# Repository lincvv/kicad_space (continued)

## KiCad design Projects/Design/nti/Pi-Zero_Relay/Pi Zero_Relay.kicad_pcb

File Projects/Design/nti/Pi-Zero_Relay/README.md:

**Board with relay for Raspberry PI Zero. There is an installation place for the Arduino shield RS-485**

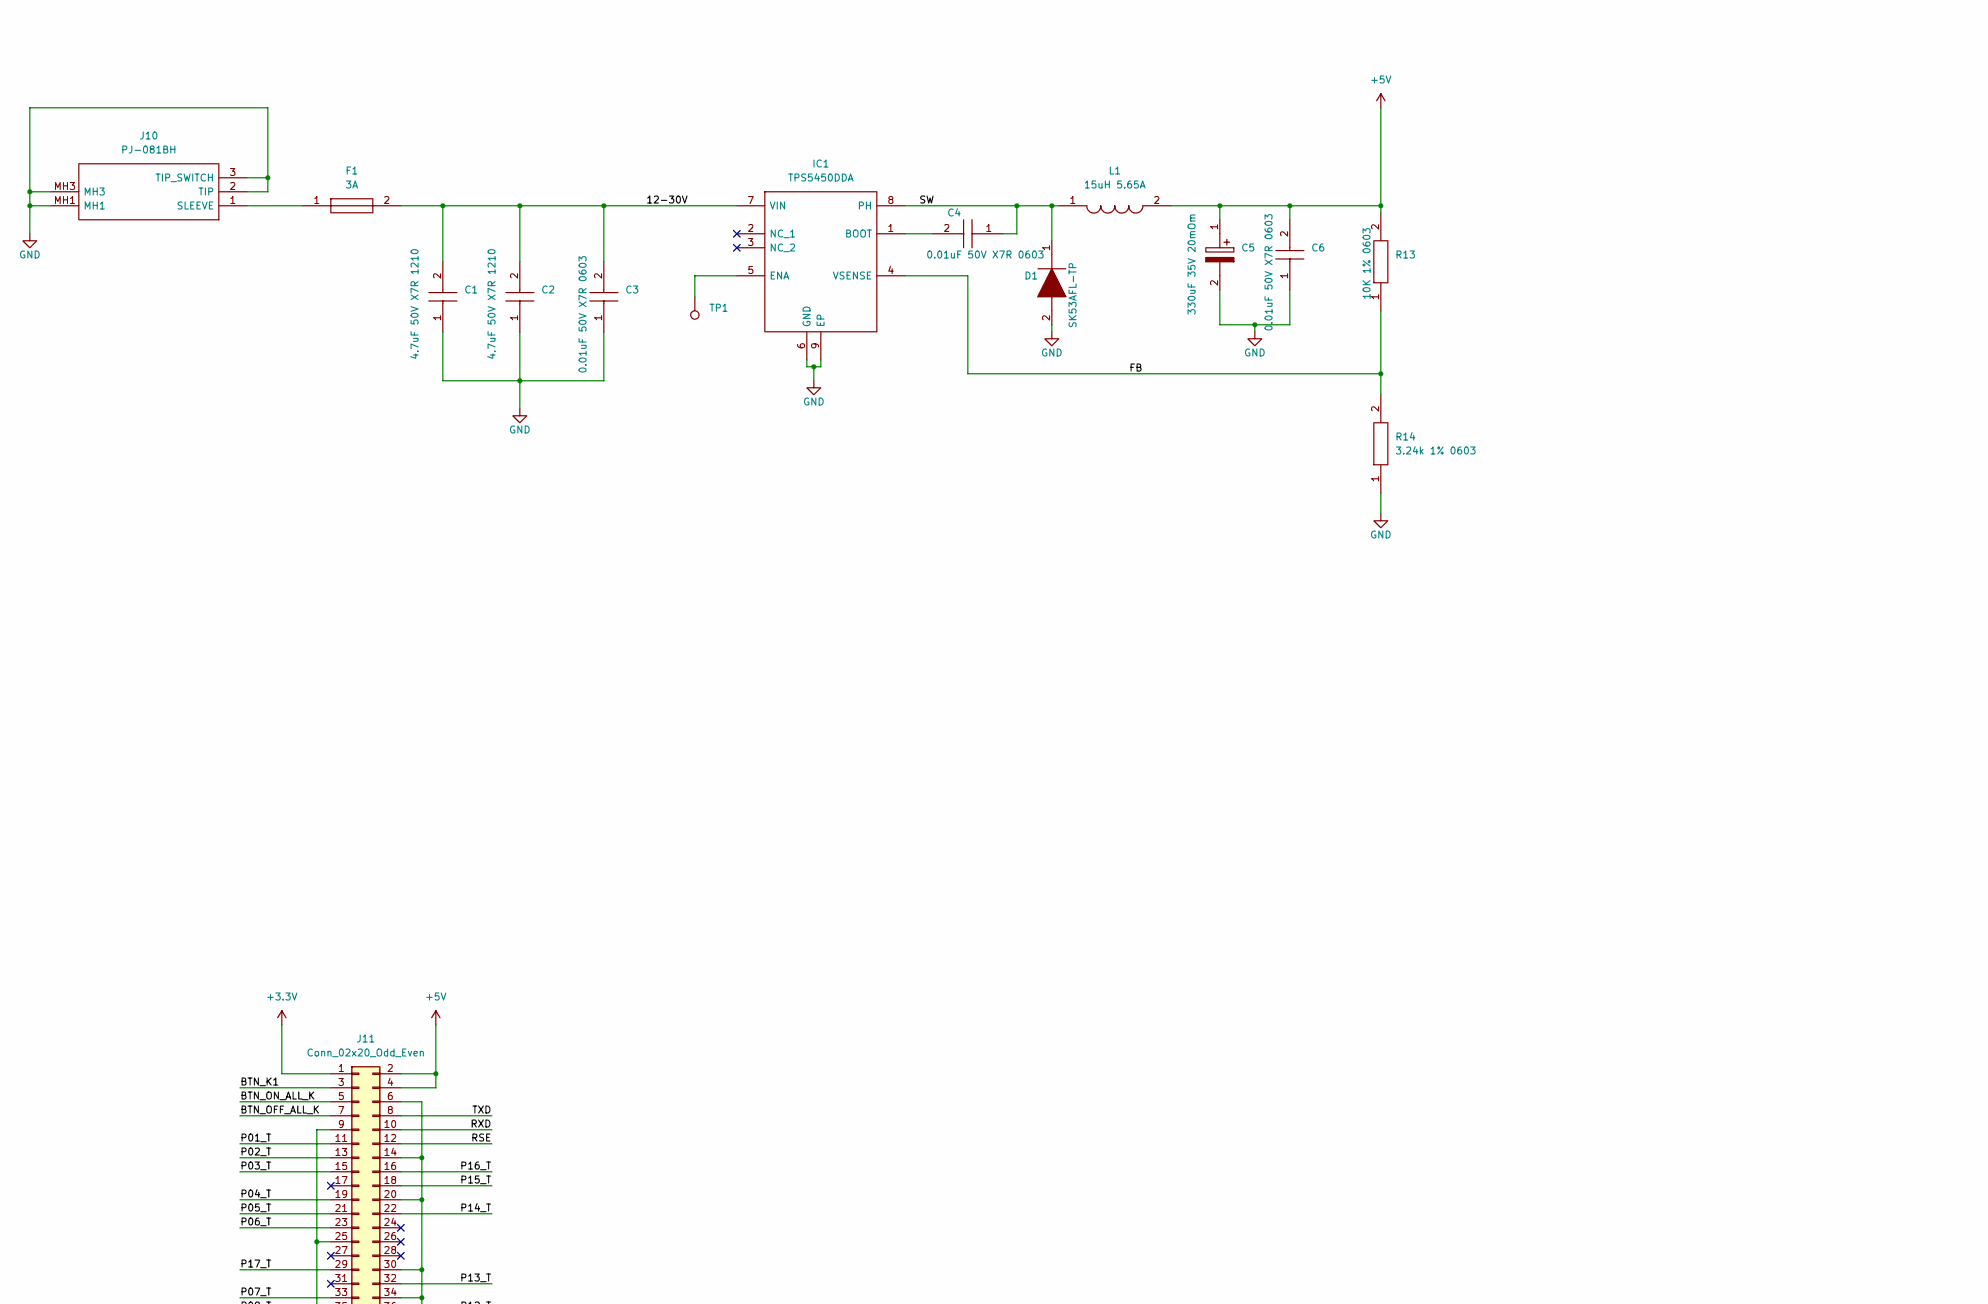
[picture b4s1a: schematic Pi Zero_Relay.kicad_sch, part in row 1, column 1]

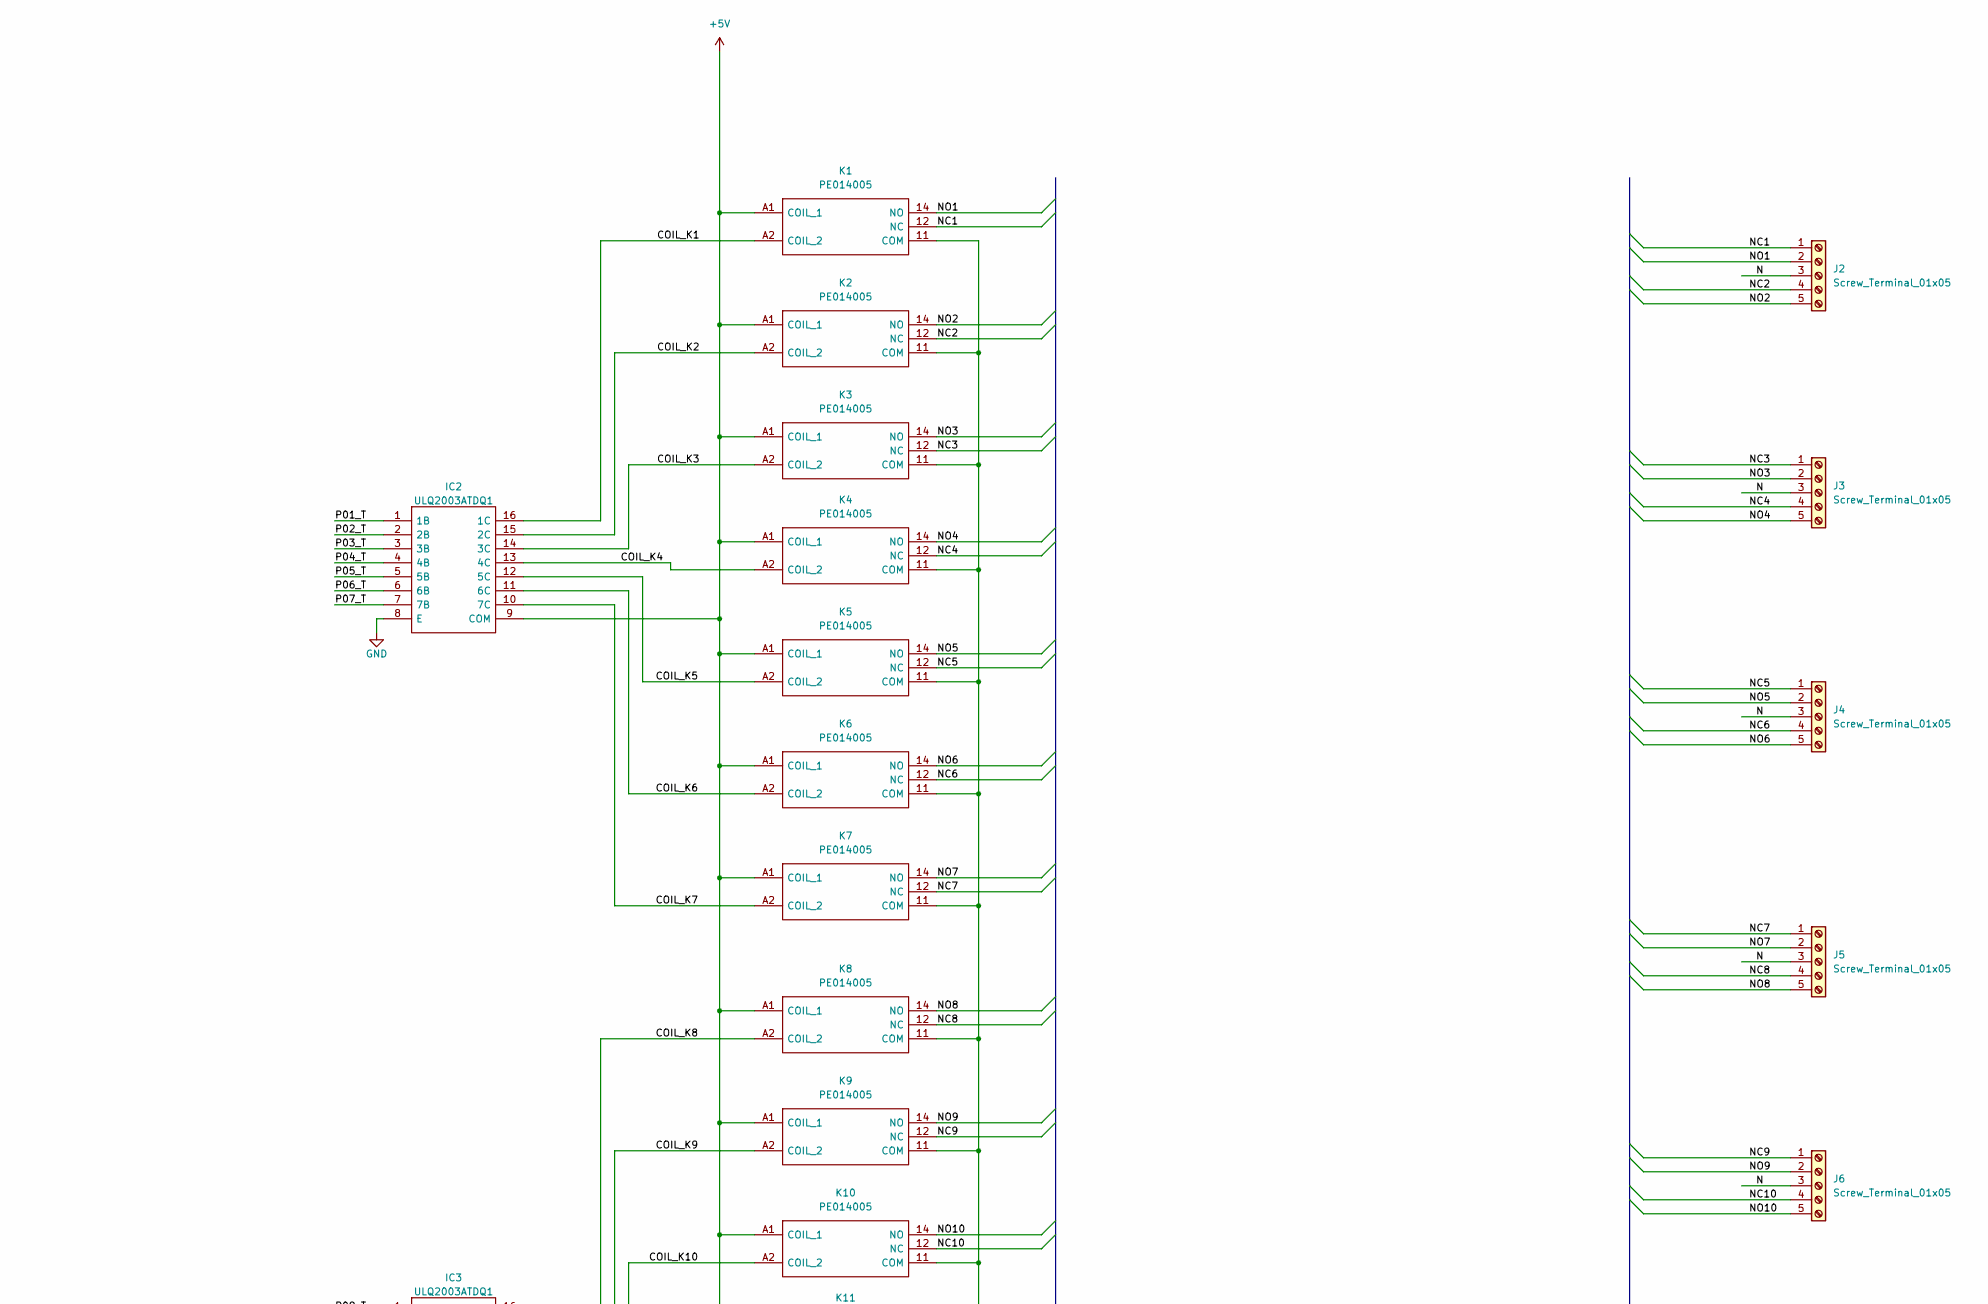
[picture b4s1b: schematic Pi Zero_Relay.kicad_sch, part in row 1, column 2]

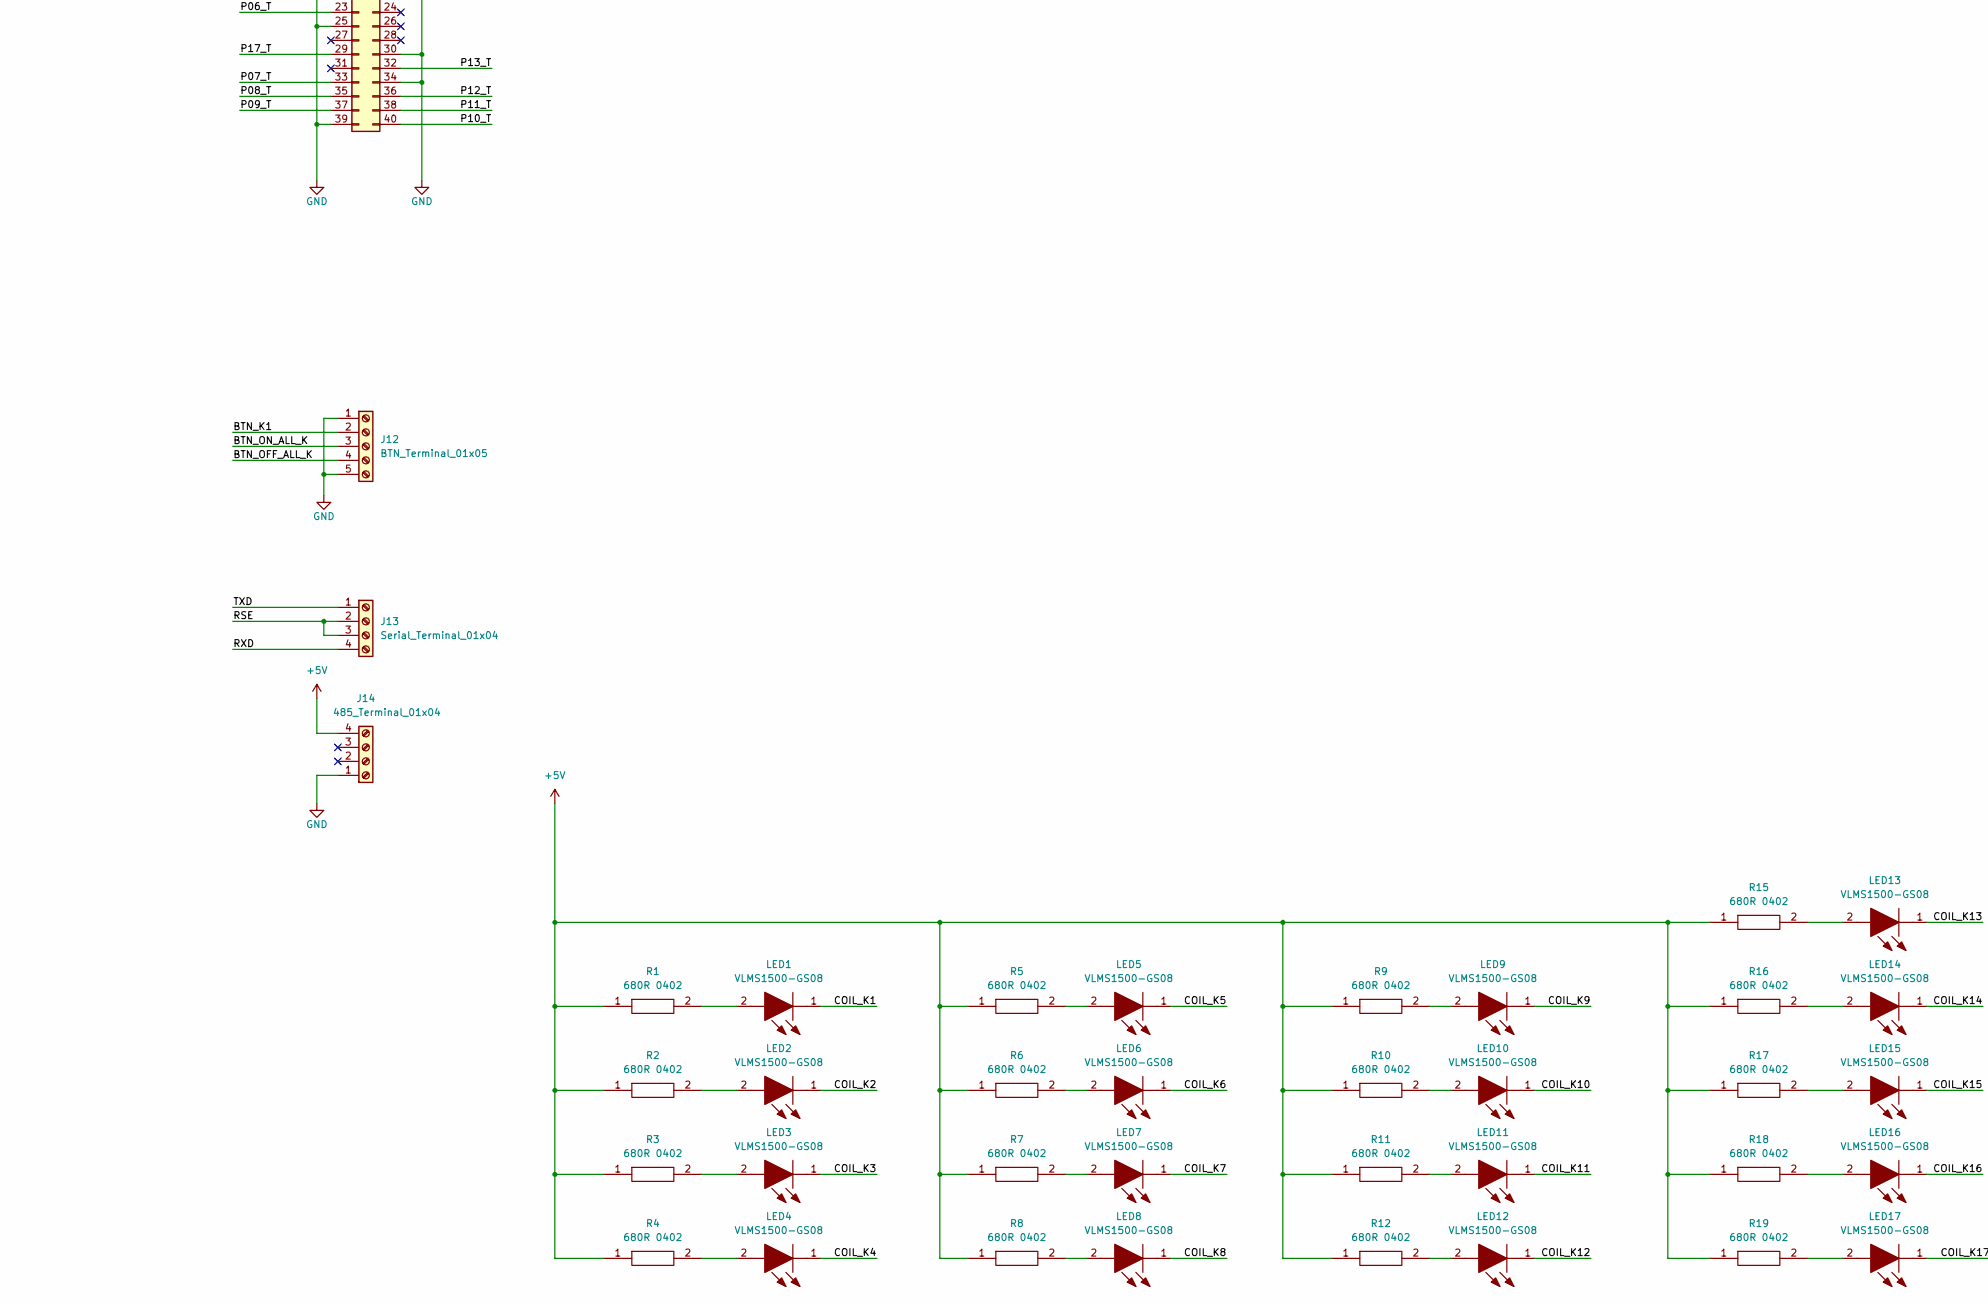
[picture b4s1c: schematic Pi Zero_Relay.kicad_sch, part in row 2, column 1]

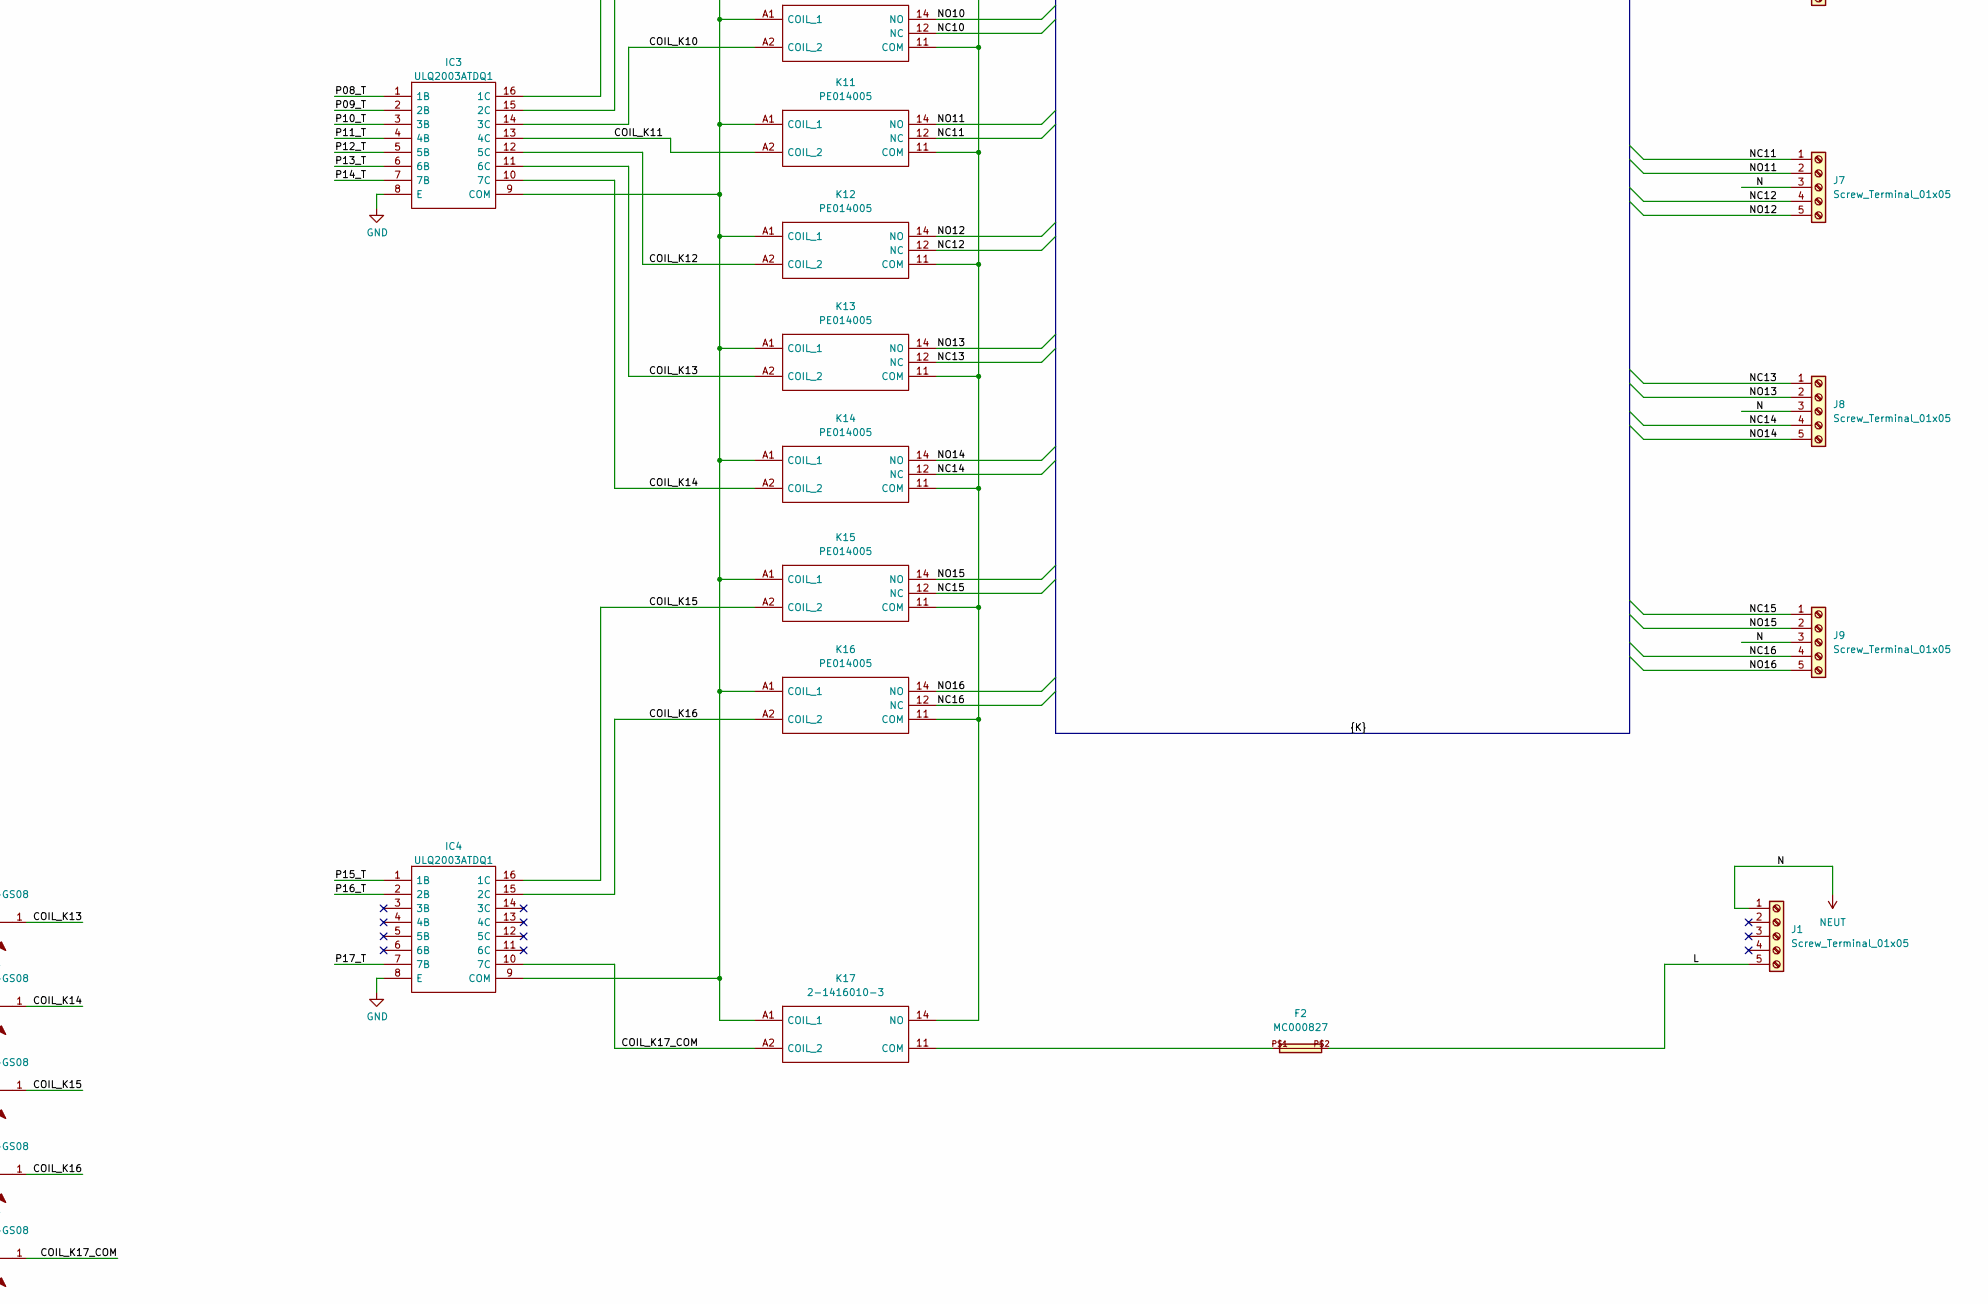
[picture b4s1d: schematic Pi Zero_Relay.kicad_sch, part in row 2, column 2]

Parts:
C1, C2: 4.7uF 50V X7R 1210; C_1210_3225Metric; Manufacturer_Part_Number CC1210KFX7R9BB475; Mouser Part Number 603-CC1210KFX7R9B475
C3, C4, C6: 0.01uF 50V X7R 0603; C_0603_1608Metric; Mouser Part Number 80-C0603C103K5RAUTO
C5: 330uF 35V 20mOm; CAPPRD530W65D1000H1050; Manufacturer_Part_Number EEH-AZK1V331B; Mouser Part Number 667-EEH-AZK1V331B
D1: SK53AFL-TP; SODFL5026X120N; Mouser Part Number 833-SK53AFL-TP
F1: 3A; Fuse_1206_3216Metric; Manufacturer_Part_Number SF-1206F300M-2
F2: MC000827
IC1: TPS5450DDA; SOIC127P600X170-9N; Mouser Part Number 595-TPS5450DDA
IC2, IC3, IC4: ULQ2003ATDQ1; SOIC127P600X175-16N; Mouser Part Number 595-ULQ2003ATDQ1
J1, J2, J3, J4, J5, J6, J7, J8, J9: Screw_Terminal_01x05; PinHeader_1x05_P2.54mm_Vertical
J10: PJ-081BH; PJ081BH; Manufacturer_Part_Number PJ-081BH; Mouser Part Number 490-PJ-081BH
J11: Conn_02x20_Odd_Even; PinHeader_2x20_P2.54mm_Vertical
J12: BTN_Terminal_01x05; PinHeader_1x05_P2.54mm_Vertical
J13: Serial_Terminal_01x04; PinHeader_1x04_P2.54mm_Vertical
J14: 485_Terminal_01x04; PinHeader_1x04_P2.54mm_Vertical
K1, K2, K3, K4, K5, K6, K7, K8, K9, K10, K11, K12, K13, K14, K15, K16: PE014005; Mouser Part Number 655-PE014005
K17: 2-1416010-3; 214160103; Mouser Part Number 655-2-1416010-3
L1: 15uH 5.65A; INDPM120120X800N; Mouser Part Number 851-CDRH127LDNP150MC
LED1, LED2, LED3, LED4, LED5, LED6, LED7, LED8, LED9, LED10, LED11, LED12, LED13, LED14, LED15, LED16, LED17: VLMS1500-GS08; VLMG1500GS08; Mouser Part Number 78-VLMS1500-GS08
R1, R2, R3, R4, R5, R6, R7, R8, R9, R10, R11, R12, R15, R16, R17, R18, R19: 680R 0402; R_0402_1005Metric; Mouser Part Number 667-ERJ-2GEJ621X
R13: 10K 1% 0603; R_0603_1608Metric; Manufacturer_Part_Number CRCW060310K0FKEAC; Mouser Part Number 71-CRCW060310K0FKEAC
R14: 3.24k 1% 0603; R_0603_1608Metric; Manufacturer_Part_Number ERJ-P03F3241V
TP1: TestPoint; TestPoint_Pad_1.5x1.5mm

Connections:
+3.3V: J11.1
+5V: C5.1, C6.2, IC2.9 (COM), IC3.9 (COM), IC4.9 (COM), J11.2, J11.4, J14.4, K1.A1 (COIL_1), K2.A1 (COIL_1), K3.A1 (COIL_1), K4.A1 (COIL_1), K5.A1 (COIL_1), K6.A1 (COIL_1), K7.A1 (COIL_1), K8.A1 (COIL_1), K9.A1 (COIL_1), K10.A1 (COIL_1), K11.A1 (COIL_1), K12.A1 (COIL_1), K13.A1 (COIL_1), K14.A1 (COIL_1), K15.A1 (COIL_1), K16.A1 (COIL_1), K17.A1 (COIL_1), L1.2, R1.1, R2.1, R3.1, R4.1, R5.1, R6.1, R7.1, R8.1, R9.1, R10.1, R11.1, R12.1, R13.2, R15.1, R16.1, R17.1, R18.1, R19.1
/12-30V: C1.2, C2.2, C3.2, F1.2, IC1.7 (VIN)
/BTN_K1: J11.3, J12.2
/BTN_OFF_ALL_K: J11.7, J12.4
/BTN_ON_ALL_K: J11.5, J12.3
/COIL_K1: IC2.16 (1C), K1.A2 (COIL_2), LED1.1
/COIL_K2: IC2.15 (2C), K2.A2 (COIL_2), LED2.1
/COIL_K3: IC2.14 (3C), K3.A2 (COIL_2), LED3.1
/COIL_K4: IC2.13 (4C), K4.A2 (COIL_2), LED4.1
/COIL_K5: IC2.12 (5C), K5.A2 (COIL_2), LED5.1
/COIL_K6: IC2.11 (6C), K6.A2 (COIL_2), LED6.1
/COIL_K7: IC2.10 (7C), K7.A2 (COIL_2), LED7.1
/COIL_K8: IC3.16 (1C), K8.A2 (COIL_2), LED8.1
/COIL_K9: IC3.15 (2C), K9.A2 (COIL_2), LED9.1
/COIL_K10: IC3.14 (3C), K10.A2 (COIL_2), LED10.1
/COIL_K11: IC3.13 (4C), K11.A2 (COIL_2), LED11.1
/COIL_K12: IC3.12 (5C), K12.A2 (COIL_2), LED12.1
/COIL_K13: IC3.11 (6C), K13.A2 (COIL_2), LED13.1
/COIL_K14: IC3.10 (7C), K14.A2 (COIL_2), LED14.1
/COIL_K15: IC4.16 (1C), K15.A2 (COIL_2), LED15.1
/COIL_K16: IC4.15 (2C), K16.A2 (COIL_2), LED16.1
/COIL_K17_COM: IC4.10 (7C), K17.A2 (COIL_2), LED17.1
/FB: IC1.4 (VSENSE), R13.1, R14.2
/L: F2.P$2, J1.5
/NC1: J2.1, K1.12 (NC)
/NC2: J2.4, K2.12 (NC)
/NC3: J3.1, K3.12 (NC)
/NC4: J3.4, K4.12 (NC)
/NC5: J4.1, K5.12 (NC)
/NC6: J4.4, K6.12 (NC)
/NC7: J5.1, K7.12 (NC)
/NC8: J5.4, K8.12 (NC)
/NC9: J6.1, K9.12 (NC)
/NC10: J6.4, K10.12 (NC)
/NC11: J7.1, K11.12 (NC)
/NC12: J7.4, K12.12 (NC)
/NC13: J8.1, K13.12 (NC)
/NC14: J8.4, K14.12 (NC)
/NC15: J9.1, K15.12 (NC)
/NC16: J9.4, K16.12 (NC)
/NO1: J2.2, K1.14 (NO)
/NO2: J2.5, K2.14 (NO)
/NO3: J3.2, K3.14 (NO)
/NO4: J3.5, K4.14 (NO)
/NO5: J4.2, K5.14 (NO)
/NO6: J4.5, K6.14 (NO)
/NO7: J5.2, K7.14 (NO)
/NO8: J5.5, K8.14 (NO)
/NO9: J6.2, K9.14 (NO)
/NO10: J6.5, K10.14 (NO)
/NO11: J7.2, K11.14 (NO)
/NO12: J7.5, K12.14 (NO)
/NO13: J8.2, K13.14 (NO)
/NO14: J8.5, K14.14 (NO)
/NO15: J9.2, K15.14 (NO)
/NO16: J9.5, K16.14 (NO)
/P01_T: IC2.1 (1B), J11.11
/P02_T: IC2.2 (2B), J11.13
/P03_T: IC2.3 (3B), J11.15
/P04_T: IC2.4 (4B), J11.19
/P05_T: IC2.5 (5B), J11.21
/P06_T: IC2.6 (6B), J11.23
/P07_T: IC2.7 (7B), J11.33
/P08_T: IC3.1 (1B), J11.35
/P09_T: IC3.2 (2B), J11.37
/P10_T: IC3.3 (3B), J11.40
/P11_T: IC3.4 (4B), J11.38
/P12_T: IC3.5 (5B), J11.36
/P13_T: IC3.6 (6B), J11.32
/P14_T: IC3.7 (7B), J11.22
/P15_T: IC4.1 (1B), J11.18
/P16_T: IC4.2 (2B), J11.16
/P17_T: IC4.7 (7B), J11.29
/RSE: J11.12, J13.2, J13.3
/RXD: J11.10, J13.4
/SW: C4.1, D1.1, IC1.8 (PH), L1.1
/TXD: J11.8, J13.1
GND: C1.1, C2.1, C3.1, C5.2, C6.1, D1.2, IC1.6 (GND), IC1.9 (EP), IC2.8 (E), IC3.8 (E), IC4.8 (E), J10.2 (TIP), J10.3 (TIP_SWITCH), J10.MH1, J10.MH3, J11.6, J11.9, J11.14, J11.20, J11.25, J11.30, J11.34, J11.39, J12.1, J12.5, J14.1, R14.1
NEUT: J1.1, J2.3, J3.3, J4.3, J5.3, J6.3, J7.3, J8.3, J9.3
unnamed: C4.2, IC1.1 (BOOT)
unnamed: F1.1, J10.1 (SLEEVE)
unnamed: IC1.5 (ENA), TP1.1
unnamed: K1.11 (COM), K2.11 (COM), K3.11 (COM), K4.11 (COM), K5.11 (COM), K6.11 (COM), K7.11 (COM), K8.11 (COM), K9.11 (COM), K10.11 (COM), K11.11 (COM), K12.11 (COM), K13.11 (COM), K14.11 (COM), K15.11 (COM), K16.11 (COM), K17.14 (NO)
unnamed: F2.P$1, K17.11 (COM)
unnamed: LED1.2, R1.2
unnamed: LED2.2, R2.2
unnamed: LED3.2, R3.2
unnamed: LED4.2, R4.2
unnamed: LED5.2, R5.2
unnamed: LED6.2, R6.2
unnamed: LED7.2, R7.2
unnamed: LED8.2, R8.2
unnamed: LED9.2, R9.2
unnamed: LED10.2, R10.2
unnamed: LED11.2, R11.2
unnamed: LED12.2, R12.2
unnamed: LED13.2, R15.2
unnamed: LED14.2, R16.2
unnamed: LED15.2, R17.2
unnamed: LED16.2, R18.2
unnamed: LED17.2, R19.2

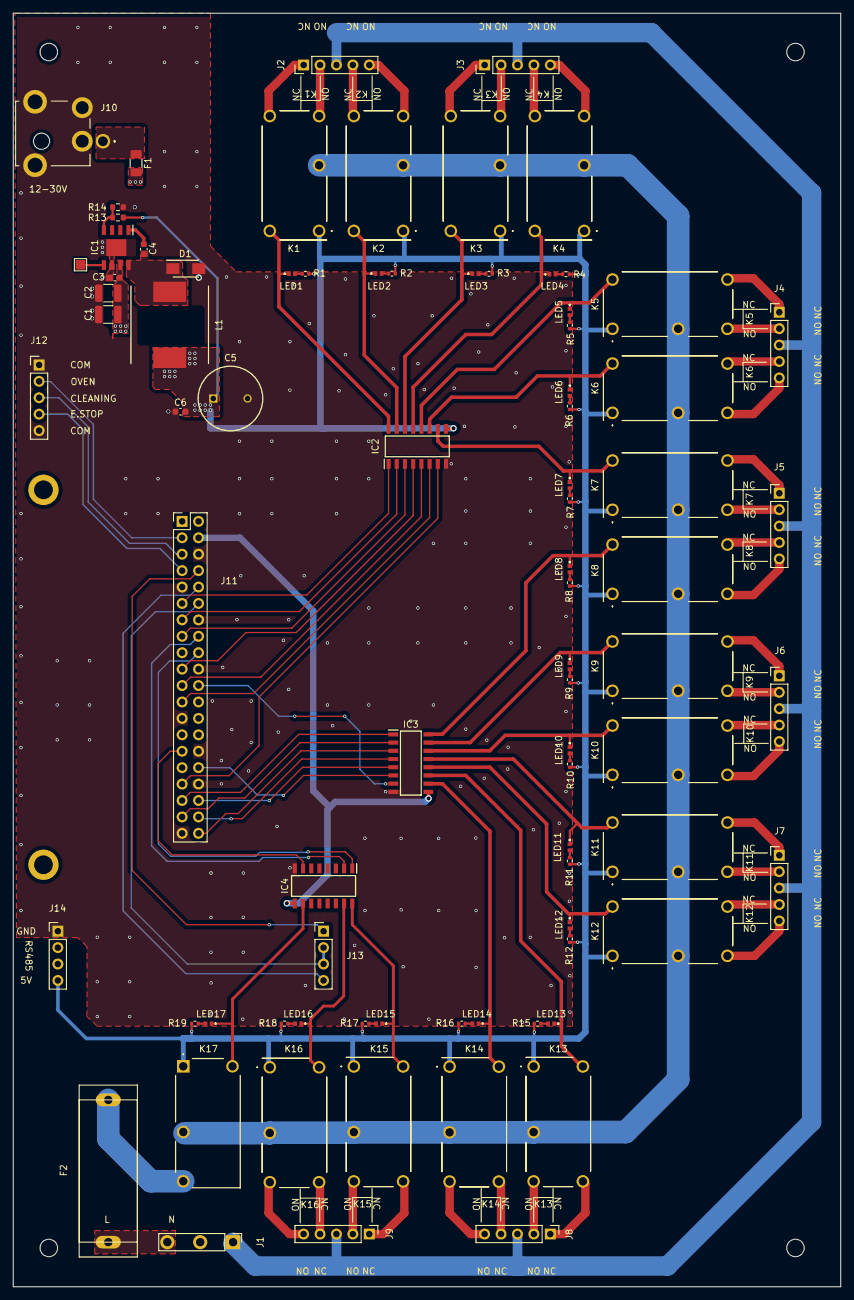
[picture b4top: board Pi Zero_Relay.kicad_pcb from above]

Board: 2 copper layers, 128.0 x 197.0 mm, 88 parts (0 on the bottom side), 101 nets.

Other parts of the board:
5, 6: MountingHole_2.7mm_M2.5_DIN965_Pad
M1, M2, M3, M4: MountingHole_2.7mm_M2.5

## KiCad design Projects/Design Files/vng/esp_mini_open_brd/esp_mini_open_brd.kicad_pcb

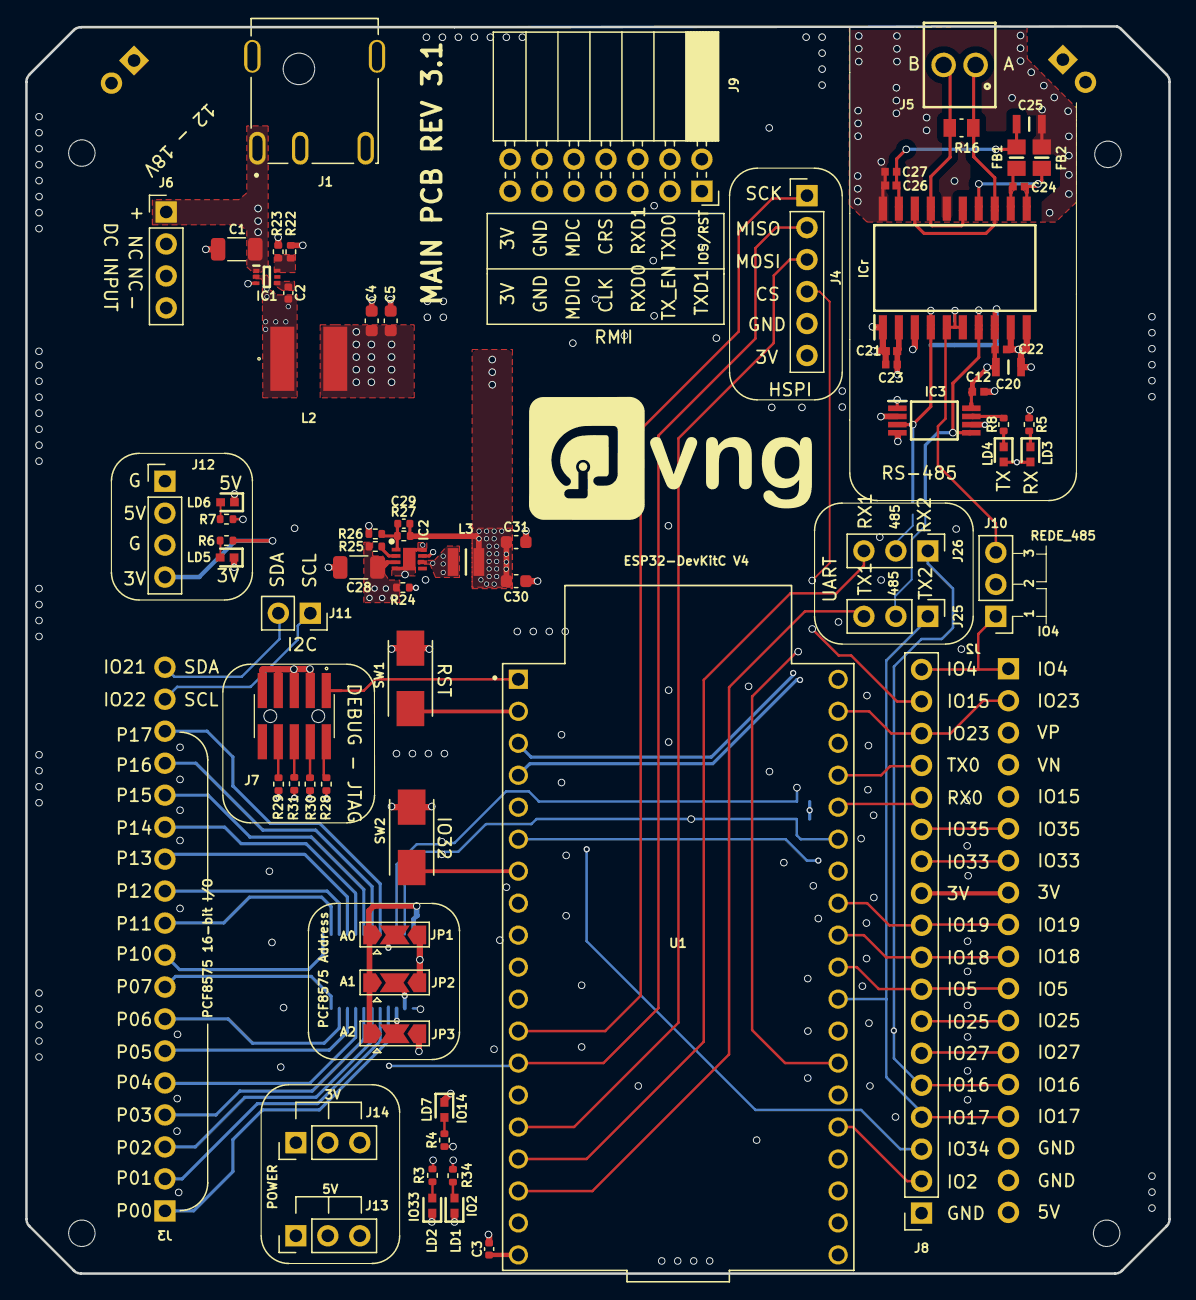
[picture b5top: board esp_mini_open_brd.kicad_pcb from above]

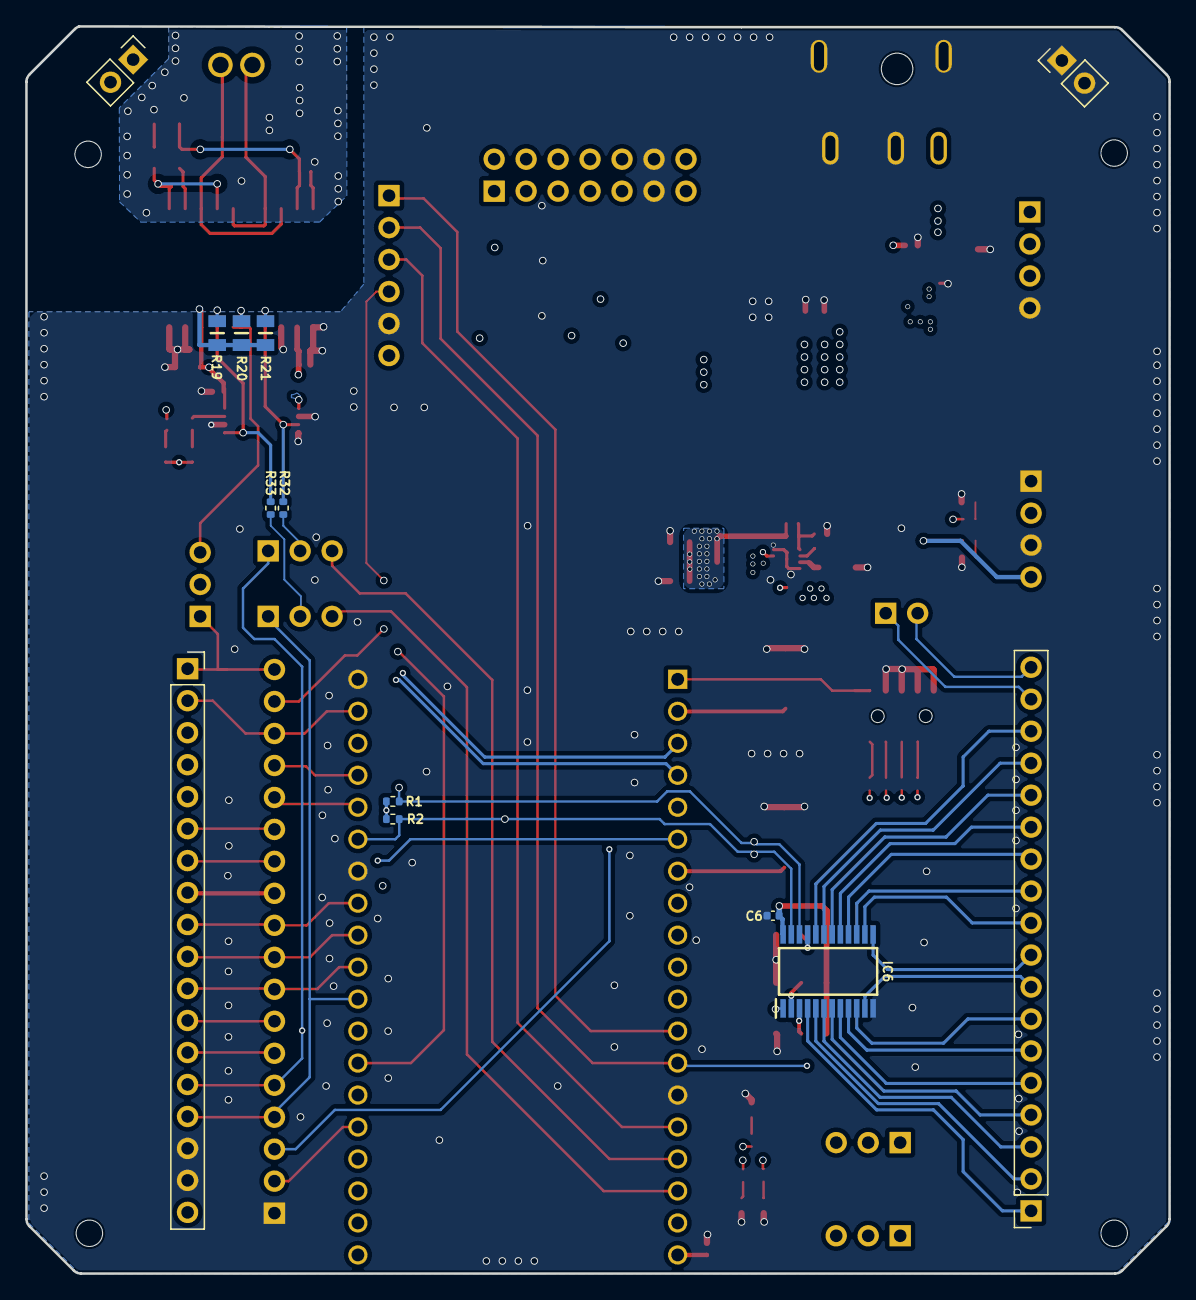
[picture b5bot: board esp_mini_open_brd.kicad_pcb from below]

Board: 4 copper layers, 90.8 x 99.1 mm, 82 parts (11 on the bottom side), 85 nets.

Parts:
C1: 10uF 25V 1206; C_1206_3216Metric
C2: 0.1uF 50V X7R 0402; C_0402_1005Metric
C3, C6: 0.1uF/16V; C_0402_1005Metric
C4, C5: 22uF 6.3V 0603; C_0603_1608Metric
C12, C22, C23, C24, C27: 0.1uF/16V; CAPC1005X55N
C20: 10uF/10V; CAPC2012X145N
C21, C26: 0.01uF/16V; CAPC1005X56N
C25: 10uF/16V; CAPC2012X145N
C28: 22uF 10V 1206 10%; C_1206_3216Metric
C29: 22pF 50V 0402 10%; C_0402_1005Metric
C30, C31: 22uF 6.3V 0603 20%; C_0603_1608Metric
FB1, FB2: 400mA/0805; BEADC2012X105N
IC1: AP62301Z6-7; SOTFL50P162X60-6N
IC2: AP3441SHE-7B; SON50P201X201X60-9N-D
IC3: LM358LVIPWR; SOP65P640X120-8N
IC6: PCF8575PWR; SOP65P640X120-24N
ICr: ADM2587EBRWZ; SOIC127P1032X265-20N
J1: PJ-079BH; DC_PW_2.5_CUI_PJ-079BH
J2: HeadersIO_Terminal_01x18; PinSocket_1x18_P2.54mm_Vertical
J3: HeadersIO(Relay)_Terminal_01x18; PinSocket_1x18_P2.54mm_Vertical
J4: HSPI_Terminal_01x06; PinHeader_1x06_P2.54mm_Vertical
J5: 691210910002
J6, J12: POWER_Terminal_01x04; PinHeader_1x04_P2.54mm_Vertical
J7: FTSH-105-01-F-DV-K-A-TR; FTSH-105-XX-YYY-DV-K-A-TR
J8: IO_Terminal_01x18; PinSocket_1x18_P2.54mm_Vertical
J9: RMII_Terminal_01x07; PinSocket_2x07_P2.54mm_Horizontal
J10: UART_REDE_Terminal_01x03; PinHeader_1x03_P2.54mm_Vertical
J11: I2C_Terminal_01x02; PinSocket_1x02_P2.54mm_Vertical
J13: EXT_5V_Terminal_01x03; PinHeader_1x03_P2.54mm_Vertical
J14: ESP_3V_Terminal_01x03; PinHeader_1x03_P2.54mm_Vertical
J25: UART_TX_Terminal_01x03; PinHeader_1x03_P2.54mm_Vertical
J26: UART_RX_Terminal_01x03; PinHeader_1x03_P2.54mm_Vertical
JP1: A0_Jumper_3_Open; SolderJumper-3_P2.0mm_Open_TrianglePad1.0x1.5mm
JP2: A1_Jumper_3_Open; SolderJumper-3_P2.0mm_Open_TrianglePad1.0x1.5mm
JP3: A2_Jumper_3_Open; SolderJumper-3_P2.0mm_Open_TrianglePad1.0x1.5mm
L2: 3.3uH 5A; VLS6045
L3: 2.2uH 2.2A; DFE2HCAH1R0MJ0L
LD1, LD4, LD7: IN-S42ATY; LEDC1005X45N
LD2, LD3: IN-S42ATG; LEDC1005X45N
LD5, LD6: IN-S42ATR; LEDC1005X55N
R1, R2, R22: 10K 1% 0402; R_0402_1005Metric
R3, R4, R5, R6, R7, R8, R34: 1K/0402; R_0402_1005Metric
R16: 120/0805; RESC2012X65N
R19, R20, R21: 10K/0805; RESC2012X60N
R23: 52.3K 1% 0402; R_0402_1005Metric
R24: 10K 0402 1% 1/16W; R_0402_1005Metric
R25: 100K 0402 1% 1/16W; R_0402_1005Metric
R26: 95.3K 0402 1% 1/10W; R_0402_1005Metric
R27: 430K 0402 1% 1/10W; R_0402_1005Metric
R28, R29, R30, R31: 100R 1% 0402; R_0402_1005Metric
R32, R33: 0R 0402; R_0402_1005Metric
SW1, SW2: 147873-1; SW_147873-1
U1: ESP32-DEVKITC; MODULE_ESP32-DEVKITC

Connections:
+3V3: C6.2, C29.2, C30.2, C31.2, IC6.24 (VCC), J2.8, J4.6, J8.11, J9.13, J9.14, J12.4, J14.1, J14.2, J14.3, JP1.1 (A), JP2.1 (A), JP3.1 (A), L3.2, R1.2, R2.2, R6.1, R27.2
+5V: C3.1, C4.2, C5.2, C12.1, C20.1, C21.1, C22.1, C23.1, C28.2, IC2.3 (VIN), IC3.8 (V+), ICr.2 (VCC_1), ICr.8 (VCC_2), J2.18, J12.2, J13.1, J13.2, J13.3, L2.2, LD3.2, LD4.2, R7.1, R19.1, R20.1, R21.1, R23.2, R24.1, R25.1, U1.19 (EXT_5V)
/A: ICr.13 (Y), ICr.18 (A), J5.1, R16.2
/A0: IC6.21 (A0), JP1.2 (C)
/A1: IC6.2 (A1), JP2.2 (C)
/A2: IC6.3 (A2), JP3.2 (C)
/ADM2587E/VISOIN: C25.1, C26.1, C27.1, FB1.2, ICr.19 (VISOIN)
/ADM2587E/VISOUT: C24.1, FB1.1, ICr.12 (VISOOUT)
/B: ICr.15 (Z), ICr.17 (B), J5.2, R16.1
/CRS/IO27: J2.13, J8.6, J9.8, U1.11 (IO27)
/EMAC_RXD1/IO26: J9.6, U1.10 (IO26)
/EN: SW1.1, U1.2 (EN)
/HSPICS0/IO15: J2.5, J4.4, J8.17, R31.2, U1.23 (IO15)
/INT_GPIO_EXP/IO35: IC6.1 (~INT), J2.6, J8.13, U1.6 (IO35)
/IO4: J2.1, J8.18, J10.1
/IO25/EMAC_RXD0: J2.12, J8.7, J9.5, U1.9 (IO25)
/IO34: J8.3, U1.5 (IO34)
/LED_CONNECT/IO33: J2.7, J8.12, R3.1, U1.8 (IO33)
/LED_TIMER/IO2: J8.2, R34.1, U1.24 (IO2)
/MISO: J4.2, R29.2, U1.13 (IO12)
/MOSI: J4.3, R30.2, U1.15 (IO13)
/MTCK: J7.4, R30.1
/MTDI: J7.8, R29.1
/MTDO: J7.6, R31.1
/MTMS: J7.2, R28.1
/P00: IC6.4 (P00), J3.1
/P01: IC6.5 (P01), J3.2
/P02: IC6.6 (P02), J3.3
/P03: IC6.7 (P03), J3.4
/P04: IC6.8 (P04), J3.5
/P05: IC6.9 (P05), J3.6
/P06: IC6.10 (P06), J3.7
/P07: IC6.11 (P07), J3.8
/P08: IC6.13 (P10), J3.9
/P09: IC6.14 (P11), J3.10
/P10: IC6.15 (P12), J3.11
/P11: IC6.16 (P13), J3.12
/P12: IC6.17 (P14), J3.13
/P13: IC6.18 (P15), J3.14
/P14: IC6.19 (P16), J3.15
/P15: IC6.20 (P17), J3.16
/PWR_DEBUG: J7.1, U1.1 (3V3)
/REDE: ICr.5 (~RE), ICr.6 (DE), J10.3, R20.2
/REDE/IO4: J10.2, U1.26 (IO4)
/REF_CLK: J9.7, U1.25 (IO0)
/RST_SSID: SW2.1, U1.7 (IO32)
/RXD0: J8.14, U1.34 (RXD0)
/RXD1: J26.3, U1.16 (SD2)
/RXD2/IO16: J2.14, J8.5, J26.1, U1.27 (IO16)
/RXD_485: IC3.3 (IN1+), ICr.4 (RXD), R21.2, R32.2
/RX_485: J26.2, R32.1
/SCK: J4.1, R4.1, R28.2, U1.12 (IO14)
/SCL/EMAC_TXD1/IO22: IC6.22 (SCL), J3.17, J9.1, J11.1, R1.1, U1.36 (IO22)
/SDA/TX_EN/IO21: IC6.23 (SDA), J3.18, J9.3, J11.2, R2.1, U1.33 (IO21)
/SENS_V_N: J2.4, U1.4 (SENSOR_VN)
/SENS_V_P: J2.3, U1.3 (SENSOR_VP)
/TXD0: J8.15, U1.35 (TXD0)
/TXD1: J25.3, U1.17 (SD3)
/TXD2/IO17: J2.15, J8.4, J25.1, U1.28 (IO17)
/TXD_485: IC3.5 (IN2+), ICr.7 (TXD), R19.2, R33.2
/TX_485: J25.2, R33.1
/VSPI_CLK/MDIO/IO18: J2.10, J8.9, J9.9, U1.30 (IO18)
/VSPI_CSO/Reset_N/IO5: J2.11, J8.8, J9.2, U1.29 (IO5)
/VSPI_MISO/EMAC_TXD0/IO19: J2.9, J8.10, J9.4, U1.31 (IO19)
/VSPI_MOSI/MDC/IO23: J2.2, J8.16, J9.10, U1.37 (IO23)
Earth_Protective: C25.2, C26.2, C27.2, FB2.2, ICr.16 (GND2_3), ICr.20 (GND2_4)
GND: C1.2, C3.2, C4.1, C5.1, C6.1, C12.2, C20.2, C21.2, C22.2, C23.2, C28.1, C30.1, C31.1, IC1.3 (GND), IC2.4 (PGND), IC2.8 (SGND), IC2.9 (EP), IC3.2 (IN1-), IC3.4 (V-), IC3.6 (IN2-), IC6.12 (GND), ICr.1 (GND1_1), ICr.3 (GND1_2), ICr.9 (GND1_3), ICr.10 (GND1_4), J1.2, J1.3, J1.S1 (SHIELD), J1.S2 (SHIELD), J2.16, J2.17, J4.5, J6.4, J7.3, J7.5, J7.7, J7.9, J8.1, J9.11, J9.12, J12.1, J12.3, JP1.3 (B), JP2.3 (B), JP3.3 (B), LD1.1, LD2.1, LD5.1, LD6.1, LD7.1, R22.1, R26.1, SW1.2, SW2.2, U1.14 (GND1), U1.32 (GND2), U1.38 (GND3)
unnamed: C2.1, IC1.4 (BST)
unnamed: IC1.6 (FB), R22.2, R23.1
unnamed: C2.2, IC1.2 (SW), L2.1
unnamed: IC2.7 (EN), R24.2
unnamed: C29.1, IC2.1 (FB), R26.2, R27.1
unnamed: IC2.6 (LX), L3.1
unnamed: IC2.2 (PG), R25.2
unnamed: IC3.1 (OUT1), R5.2
unnamed: IC3.7 (OUT2), R8.2
unnamed: C24.2, FB2.1, ICr.11 (GND2_1), ICr.14 (GND2_2)
unnamed: LD1.2, R34.2
unnamed: LD2.2, R3.2
unnamed: LD3.1, R5.1
unnamed: LD4.1, R8.1
unnamed: LD5.2, R6.2
unnamed: LD6.2, R7.2
unnamed: LD7.2, R4.2
V+: C1.1, IC1.1 (VIN), J1.1, J6.1

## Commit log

2024-06-23 init
2024-06-23 update soil sens
2024-06-23 del duplicate
